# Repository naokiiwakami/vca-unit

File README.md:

# vca-unit

WARNING: The module has not been fully tested yet!

This is a compact VCA (Voltage-Controlled Amplifier) unit that operates without any additional
external components. Its small form factor — approximately 22mm × 10.5mm — makes it ideal for
integration as a submodule in larger synthesizer projects. The module features six pins arranged
in two rows with a 2.54mm pitch, spaced seven pitches apart. It is also compatible with standard
breadboards..

The unit has been tested with a ±12V symmetrical power supply. Basic specifications are as follows:

- **Input signal range:** -8V to +8V (recommended: -5V to +5V)
- **CV range**: 0V to 8V *(unity gain is achieved at approximately 4.6V)*

Below is a simple usage of the module.

This repository includes the KiCad project files, along with the symbol and footprint for the unit.

The schematic is shown below.  Assembly does not require any trimming or calibration.

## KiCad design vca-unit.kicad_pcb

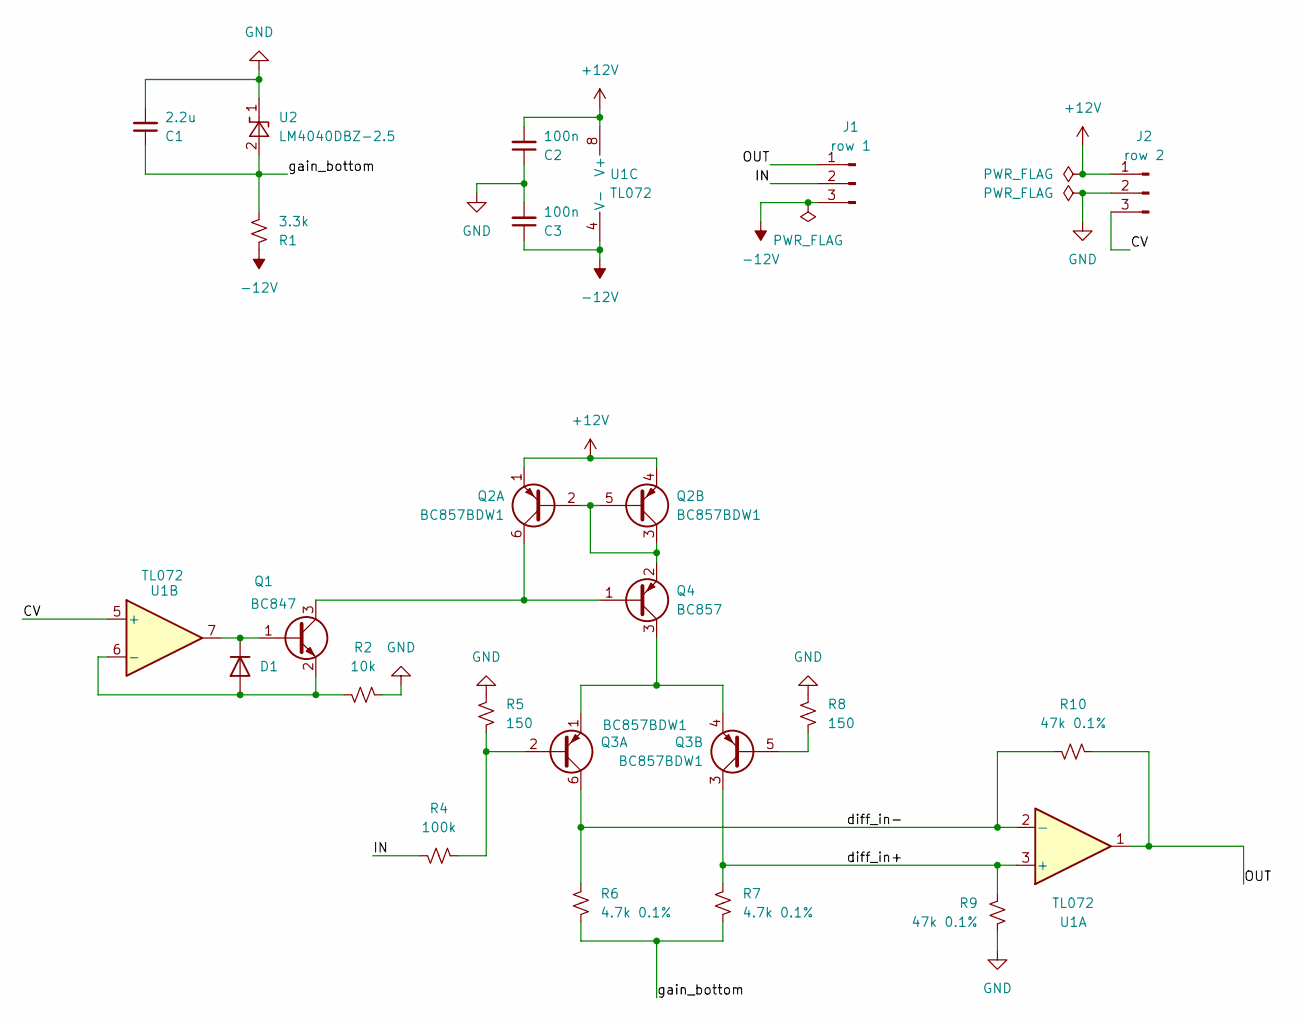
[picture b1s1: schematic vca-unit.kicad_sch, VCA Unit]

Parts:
C1: 2.2u; C_0603_1608Metric_Pad1.08x0.95mm_HandSolder
C2, C3: 100n; C_0603_1608Metric_Pad1.08x0.95mm_HandSolder
D1: 1N4148; D_SOD-323_HandSoldering
J1: row 1; PinHeader_1x03_P2.54mm_Vertical
J2: row 2; PinHeader_1x03_P2.54mm_Vertical
Q1: BC847; SOT-23
Q2, Q3: BC857BDW1; SOT-363_SC-70-6
Q4: BC857; SOT-23
R1: 3.3k; R_0603_1608Metric_Pad0.98x0.95mm_HandSolder
R2: 10k; R_0603_1608Metric_Pad0.98x0.95mm_HandSolder
R4: 100k; R_0603_1608Metric_Pad0.98x0.95mm_HandSolder
R5, R8: 150; R_0603_1608Metric_Pad0.98x0.95mm_HandSolder
R6, R7: 4.7k 0.1%; R_0603_1608Metric_Pad0.98x0.95mm_HandSolder
R9, R10: 47k 0.1%; R_0603_1608Metric_Pad0.98x0.95mm_HandSolder
U1: TL072; SOT-23-8_Handsoldering
U2: LM4040DBZ-2.5; SOT-23

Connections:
+12V: C2.2, J2.1, Q2.1 (E1), Q2.4 (E2), U1.8 (V+)
-12V: C3.1, J1.3, R1.1, U1.4 (V-)
/CV: J2.3, U1.5 (+)
/IN: J1.2, R4.2
/OUT: J1.1, R10.2, U1.1
/diff_in+: Q3.3 (C2), R7.1, R9.2, U1.3 (+)
/diff_in-: Q3.6 (C1), R6.1, R10.1, U1.2 (-)
/gain_bottom: C1.1, R1.2, R6.2, R7.2, U2.2 (A)
GND: C1.2, C2.1, C3.2, J2.2, R2.1, R5.1, R8.1, R9.1, U2.1 (K)
unnamed: D1.2 (A), Q1.2 (E), R2.2, U1.6 (-)
unnamed: D1.1 (K), Q1.1 (B), U1.7
unnamed: Q1.3 (C), Q2.6 (C1), Q4.1 (B)
unnamed: Q2.2 (B1), Q2.3 (C2), Q2.5 (B2), Q4.2 (E)
unnamed: Q3.2 (B1), R4.1, R5.2
unnamed: Q3.1 (E1), Q3.4 (E2), Q4.3 (C)
unnamed: Q3.5 (B2), R8.2

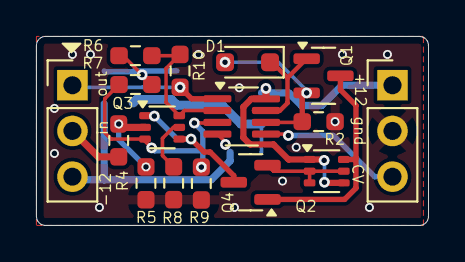
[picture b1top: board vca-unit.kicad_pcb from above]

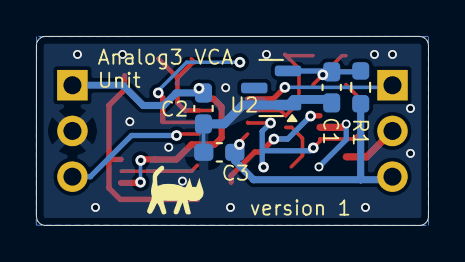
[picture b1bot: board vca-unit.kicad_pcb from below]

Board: 2 copper layers, 21.8 x 10.5 mm, 21 parts (5 on the bottom side), 16 nets.

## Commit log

2025-06-10 Fix schematic
2025-06-10 Update the schematic in doc again
